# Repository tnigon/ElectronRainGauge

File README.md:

# Electron Weather Station

## Summary
This repository contains the files that I used to create a "cloud-connected" weather station via the [Particle Electron](https://store.particle.io/collections/electron). Please see [my how-to guide](http://tylernigon.me/projects/weather_station.html) describing the steps I took.

## Files
- The [circuit_board](https://github.com/tnigon/Electron_weather-station/tree/master/circuit_board) folder contains items for designing and manufacturing the printed circuit board (pcb).
- The [particle_code](https://github.com/tnigon/Electron_weather-station/tree/master/particle_code) folder contains the .ino files that contain the user-readable Particle code. These can be loaded or copied and pasted into Particle's [IDE](https://build.particle.io/build) to modify the code and/or compile to binary.
- [binary](https://github.com/tnigon/Electron_weather-station/tree/master/binary) contains a blank binary file that can be flashed to the Electron to stop publishing. This came in handy for me when troubleshooting my code and I didn't quite have it right.
- [webhook_templates](https://github.com/tnigon/Electron_weather-station/tree/master/webhook_templates) contains webhook templates for publishing your data to ThingSpeak or Weather Underground. Note that device ID and webhook name should be modified to be used with your device.

## Author
- [Tyler Nigon](https://tylernigon.me)

## License
This project is licensed under the GNU General Public License - see the [LICENSE.md](https://github.com/tnigon/Electron_weather-station/blob/master/LICENSE) for details

## Change log
- v2.0:
- v2.1:
- v2.2:

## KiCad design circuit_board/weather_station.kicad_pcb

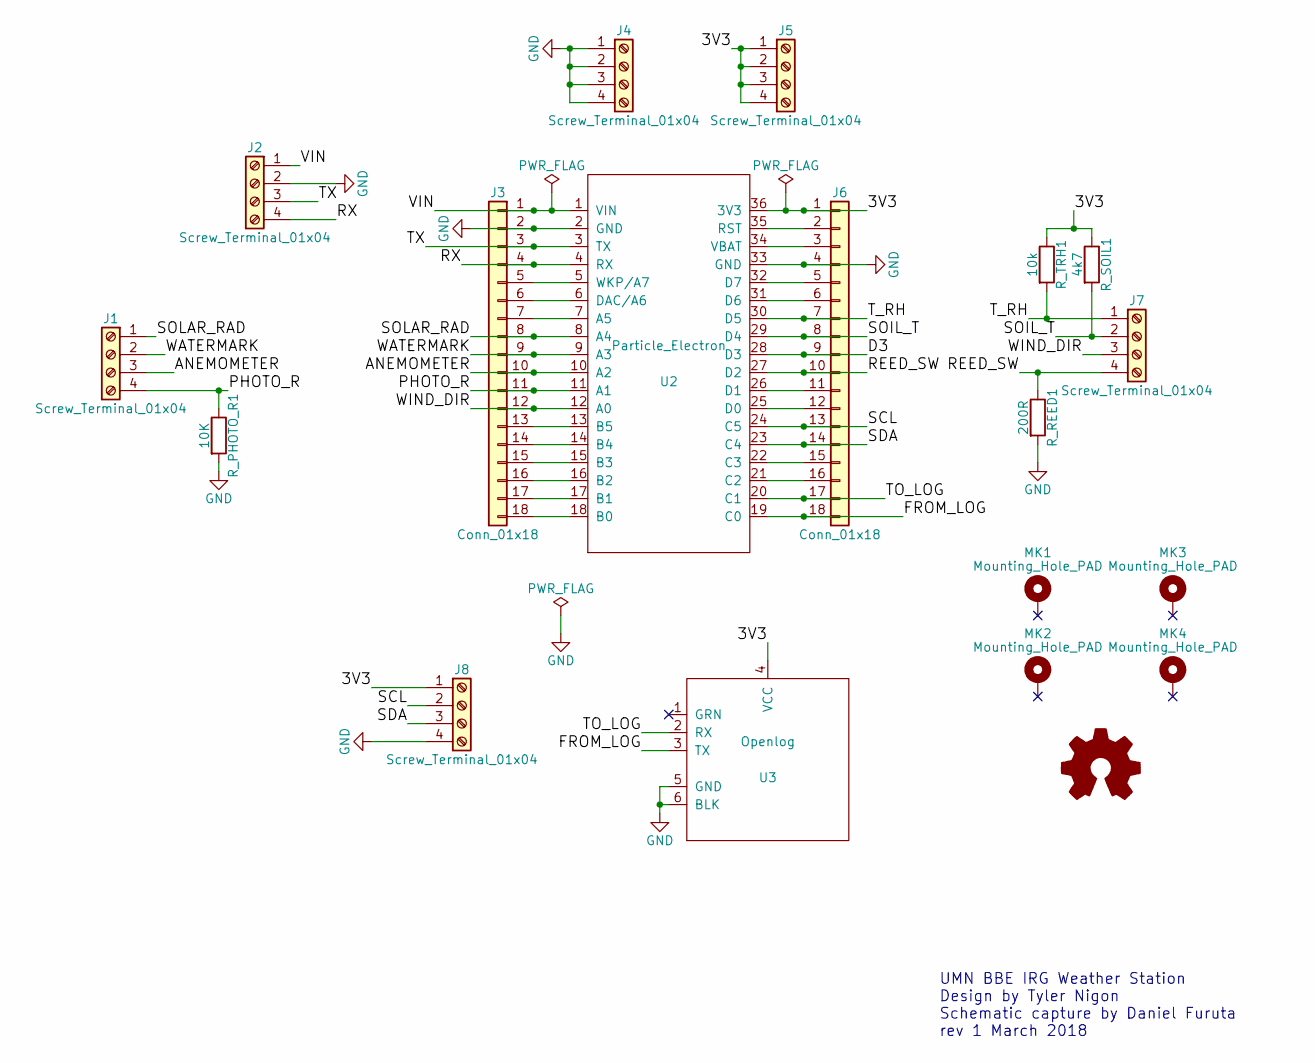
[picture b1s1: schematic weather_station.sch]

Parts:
J1, J2, J4, J5, J7, J8: Screw_Terminal_01x04; TerminalBlock_04x3.5mm_Straight
J3, J6: Conn_01x18; Pin_Header_Straight_1x18_Pitch2.54mm
MK1, MK2, MK3, MK4: Mounting_Hole_PAD; MountingHole_3mm_Pad
R_PHOTO_R1: 10K; R_TH_0.25W_400mil
R_REED1: 200R; R_TH_0.25W_400mil
R_SOIL1: 4k7; R_TH_0.25W_400mil
R_TRH1: 10k; R_TH_0.25W_400mil
U2: Particle_Electron
U3: Openlog

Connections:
/3V3: J5.1, J5.2, J5.3, J5.4, J6.1, J8.1, R_SOIL1.1, R_TRH1.1, U2.36 (3V3), U3.4 (VCC)
/ANEMOMETER: J1.3, J3.10, U2.10 (A2)
/D3: J6.9, U2.28 (D3)
/FROM_LOG: J6.18, U2.19 (C0), U3.3 (TX)
/PHOTO_R: J1.4, J3.11, R_PHOTO_R1.1, U2.11 (A1)
/REED_SW: J6.10, J7.4, R_REED1.1, U2.27 (D2)
/RX: J2.4, J3.4, U2.4 (RX)
/SCL: J6.13, J8.2, U2.24 (C5)
/SDA: J6.14, J8.3, U2.23 (C4)
/SOIL_T: J6.8, J7.2, R_SOIL1.2, U2.29 (D4)
/SOLAR_RAD: J1.1, J3.8, U2.8 (A4)
/TO_LOG: J6.17, U2.20 (C1), U3.2 (RX)
/TX: J2.3, J3.3, U2.3 (TX)
/T_RH: J6.7, J7.1, R_TRH1.2, U2.30 (D5)
/VIN: J2.1, J3.1, U2.1 (VIN)
/WATERMARK: J1.2, J3.9, U2.9 (A3)
/WIND_DIR: J3.12, J7.3, U2.12 (A0)
GND: J2.2, J3.2, J4.1, J4.2, J4.3, J4.4, J6.4, J8.4, R_PHOTO_R1.2, R_REED1.2, U2.2 (GND), U2.33 (GND), U3.5 (GND), U3.6 (BLK)
unnamed: J3.5, U2.5 (WKP/A7)
unnamed: J3.6, U2.6 (DAC/A6)
unnamed: J3.7, U2.7 (A5)
unnamed: J3.13, U2.13 (B5)
unnamed: J3.14, U2.14 (B4)
unnamed: J3.15, U2.15 (B3)
unnamed: J3.16, U2.16 (B2)
unnamed: J3.17, U2.17 (B1)
unnamed: J3.18, U2.18 (B0)
unnamed: J6.2, U2.35 (RST)
unnamed: J6.3, U2.34 (VBAT)
unnamed: J6.5, U2.32 (D7)
unnamed: J6.6, U2.31 (D6)
unnamed: J6.11, U2.26 (D1)
unnamed: J6.12, U2.25 (D0)
unnamed: J6.15, U2.22 (C3)
unnamed: J6.16, U2.21 (C2)

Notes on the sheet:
UMN BBE IRG Weather Station Design by Tyler Nigon Schematic capture by Daniel Furuta rev 1 March 2018

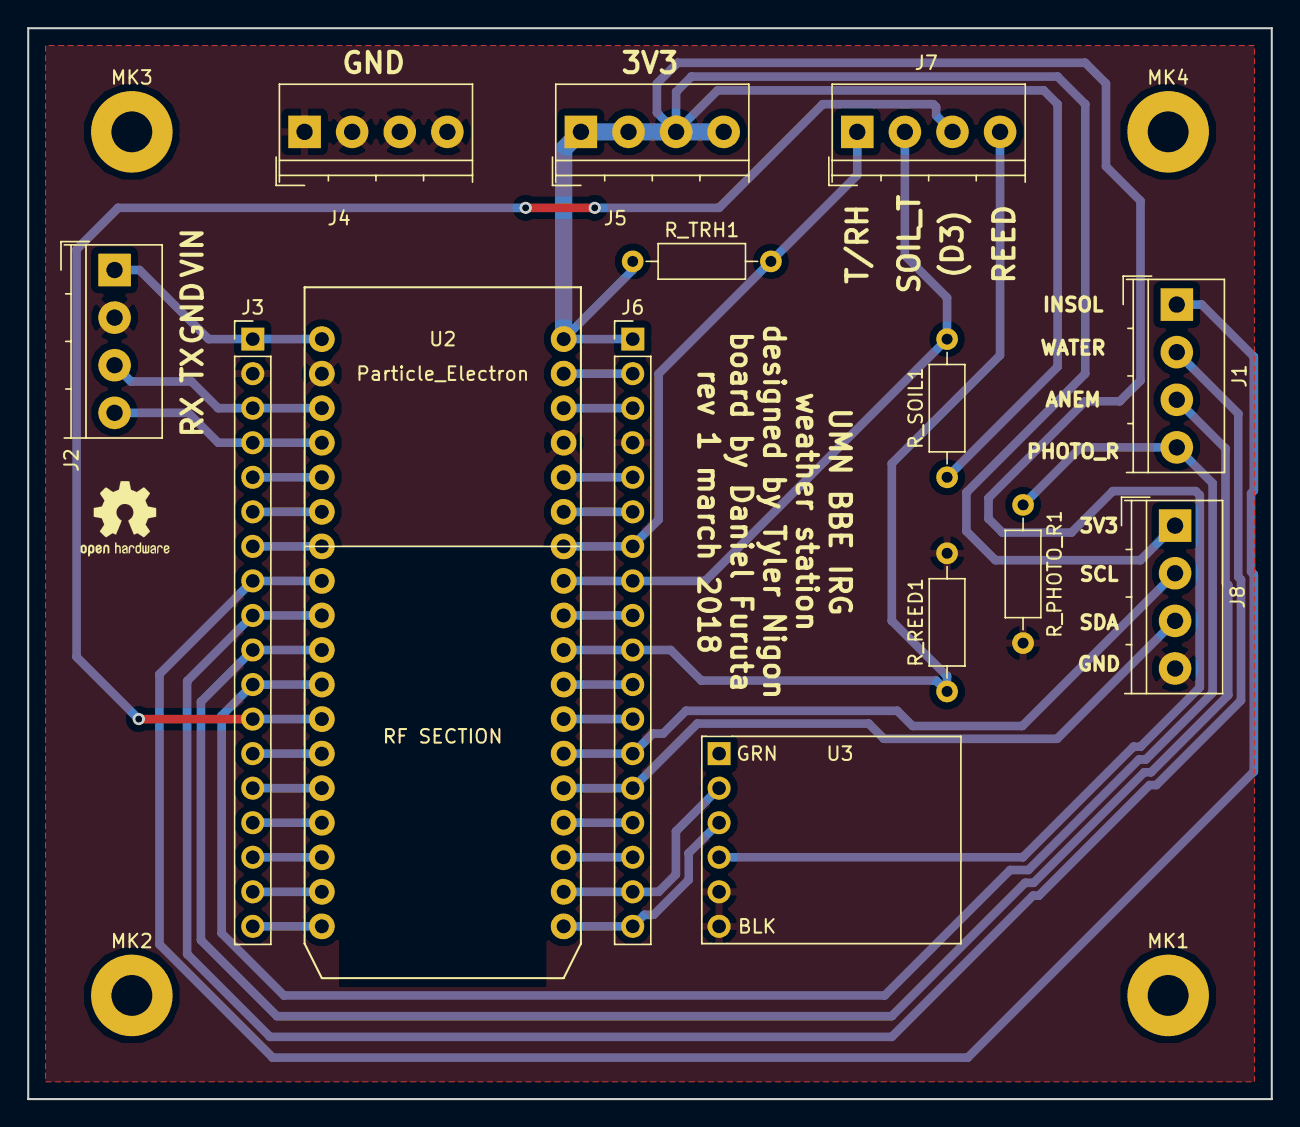
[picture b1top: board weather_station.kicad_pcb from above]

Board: 2 copper layers, 91.4 x 78.7 mm, 18 parts (0 on the bottom side), 35 nets.

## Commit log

2017-04-13 Sending data every 30 minutes on top and bottom of the hour
2017-04-25 fritzing wiring diagram added
2017-05-02 updating the anemometer for voltage output
2017-06-21 adding webhook json for weather underground
2017-06-28 updated binary electron code supporting weather underground
2017-06-28 adding support to publish daily rain data to wunderground
2017-06-30 changed thingspeak webhook json
2017-06-30 cleaning up .ino files
2017-07-10 adding updated .ino file
2017-07-15 cleaning up files
2017-07-19 updating readme
2017-07-20 Create LICENSE
2017-07-20 adding license info
2017-08-09 updating .ino for more time flexibility
2017-12-11 version 2 of weather station user firmware for Electron
2017-12-11 Delete electron_weather.ino
    Added v2 of user firmware
2018-03-14 adding PCB breakout board
2018-04-06 adding pdf
2018-04-26 adding v2.2 and organizing into folders
2018-04-26 adding webhook templates
2018-04-26 remove .fzz
2018-04-26 removing redundant files
2018-04-26 changing name of 2.0
2018-04-26 removing
2018-04-27 cleaning root
2018-04-27 correcting solar radiation equations
2018-06-17 be sure year is not 1999
2018-12-12 correcting watermark equation and removing unused libraries
2019-04-29 v2.5 weather code
